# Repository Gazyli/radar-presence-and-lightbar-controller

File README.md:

# Custom ESPhome Devices for Home Assistant

This repository contains the hardware designs and custom firmware for two integrated smart home devices designed from scratch: a **mmWave radar presence sensor** and a **dual-channel CCT light controller**.

## Overview

The two devices are built around the ESP32-C3 microcontroller and are designed to seamlessly integrate with Home Assistant via ESPHome. The presence sensor utilizes advanced mmWave radar technology for accurate spatial tracking, while the light controller offers precise control over brightness and color temperature for LED lighting setups. Both devices are designed with modular firmware configurations to allow for easy customization and deployment across multiple nodes in a smart home environment.

## Devices

### 1. mmWave Radar Presence Sensor
A highly sensitive presence detection node utilizing mmWave radar technology (supporting LD2410C and LD2450 sensors).
* **Features**: Real-time spatial tracking with custom zone/target math logic, combined with integrated environmental monitoring (temperature, humidity, light levels).
* **Hardware**: Custom PCBs designed in KiCad, powered by ESP32-C3 microcontrollers.
* **Firmware**: Modular ESPHome configuration leveraging custom C++ headers (`radar_math.h`, `zone_math.h`) for complex tracking.

### 2. Dual-Channel CCT Light Controller (Lightbar)
A precision lighting controller tailored for dual-channel (warm/cool white) LED strips.
* **Features**: Precise, flicker-free adjustment of brightness and color temperature (CCT). Also supports ambient light sensors (e.g., BH1750) for dynamic lighting capabilities. Powered with USB-PD.
* **Hardware**: Custom KiCad schematic and PCB layout for LED driving and ESP32 control.
* **Firmware**: ESPHome configurations optimized for smooth dimming logic and color temperature transitions.

## Project Structure

* **`ESPhome/`**: Contains all firmware configurations and code.
  * `common/`: Reusable YAML fragments (base ESP32 setups, sensor integrations) and custom C++ header files used across multiple identical device nodes.
  * `lightbar/`: Deployment-specific configurations for the CCT light controllers.
  * `presence/`: Deployment-specific configurations for the presence sensors.
* **`schematics/`**: KiCad project files (`.kicad_sch`, `.kicad_pcb`) containing the circuit designs for both the presence sensor and light controller variants.
* **`enclosures/`**: 3D printable enclosure designs for both devices, including STL and 3MF files.

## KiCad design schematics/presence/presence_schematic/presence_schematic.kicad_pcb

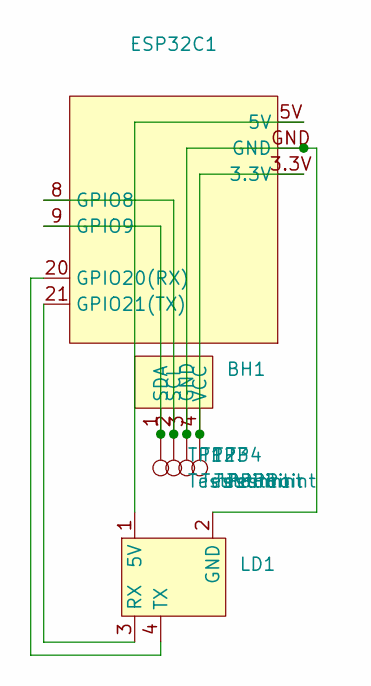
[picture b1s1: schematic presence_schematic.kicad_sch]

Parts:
BH1: BH1750
ESP32C1: ESP32-C3 supermini
LD1: LD2450
TP1, TP2, TP3, TP4: TestPoint; SolderWirePad_1x01_SMD_1.5x3mm

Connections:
unnamed: BH1.3 (GND), ESP32C1.GND, LD1.2 (GND), TP3.1
unnamed: BH1.2 (SCL), ESP32C1.8 (GPIO8), TP2.1
unnamed: BH1.1 (SDA), ESP32C1.9 (GPIO9), TP1.1
unnamed: BH1.4 (VCC), ESP32C1.3.3V, TP4.1
unnamed: ESP32C1.20 (GPIO20(RX)), LD1.4 (TX)
unnamed: ESP32C1.21 (GPIO21(TX)), LD1.3 (RX)
unnamed: ESP32C1.5V, LD1.1 (5V)

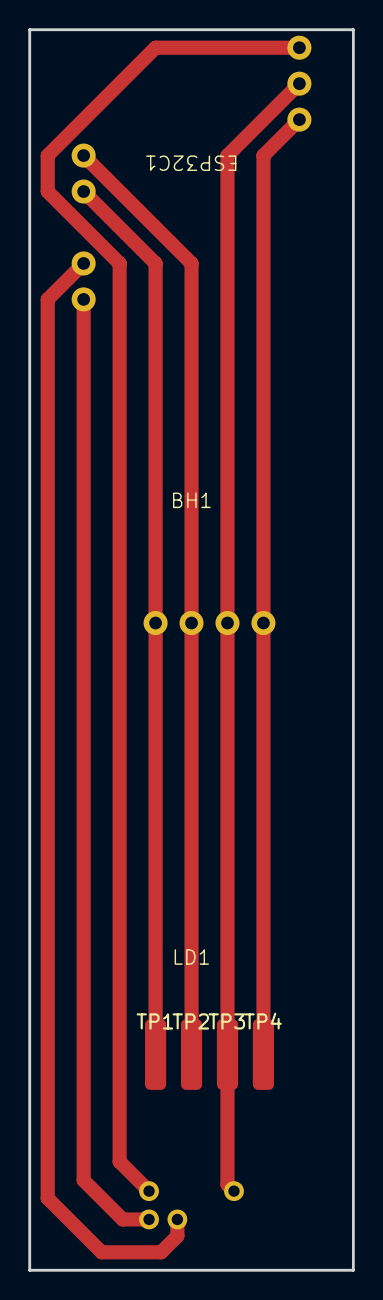
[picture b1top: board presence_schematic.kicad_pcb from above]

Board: 2 copper layers, 22.9 x 87.6 mm, 7 parts (0 on the bottom side), 7 nets.

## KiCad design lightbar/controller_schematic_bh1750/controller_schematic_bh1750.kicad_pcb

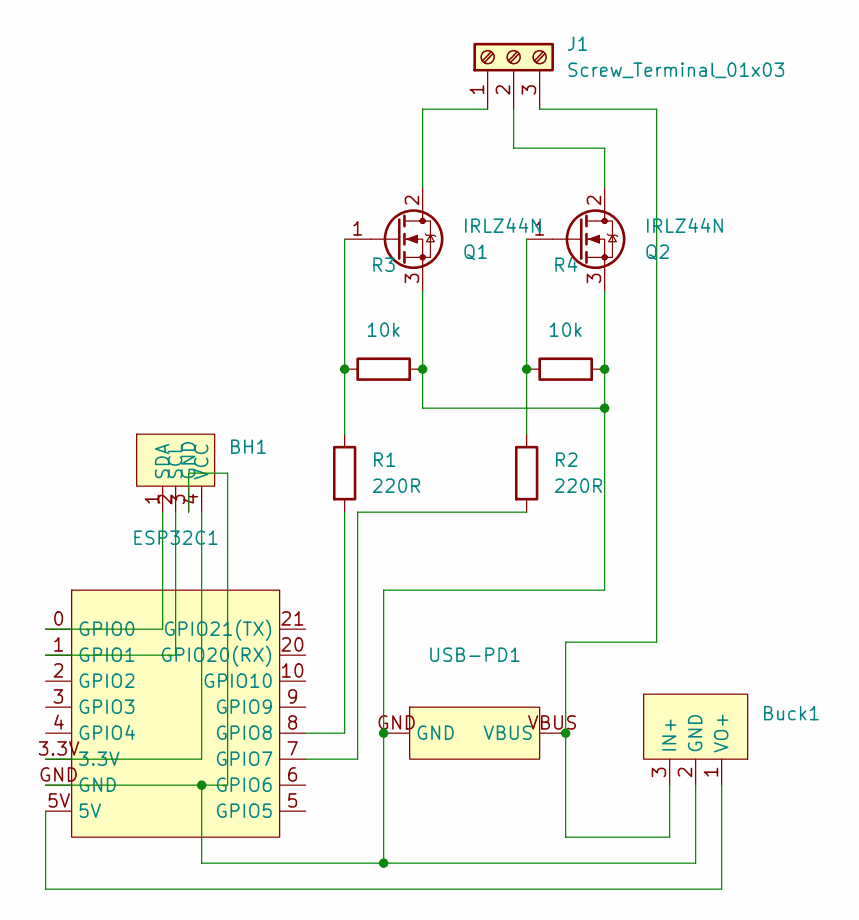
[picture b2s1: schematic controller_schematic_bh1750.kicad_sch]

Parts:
BH1: BH1750
Buck1: Buck_converter
ESP32C1: ESP32-C3 supermini
J1: Screw_Terminal_01x03; 3 pin screw connector
Q1, Q2: IRLZ44N; TO-220-3_Horizontal_TabDown
R1, R2: 220R; R_Axial_DIN0207_L6.3mm_D2.5mm_P7.62mm_Horizontal
R3, R4: 10k; R_Axial_DIN0207_L6.3mm_D2.5mm_P7.62mm_Horizontal
USB-PD1: USB-PD board

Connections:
unnamed: BH1.3 (GND), Buck1.2 (GND), ESP32C1.GND, Q1.3 (S), Q2.3 (S), R3.2, R4.2, USB-PD1.GND
unnamed: BH1.2 (SCL), ESP32C1.1 (GPIO1)
unnamed: BH1.1 (SDA), ESP32C1.0 (GPIO0)
unnamed: BH1.4 (VCC), ESP32C1.3.3V
unnamed: Buck1.3 (IN+), J1.3, USB-PD1.VBUS
unnamed: Buck1.1 (VO+), ESP32C1.5V
unnamed: ESP32C1.7 (GPIO7), R2.2
unnamed: ESP32C1.8 (GPIO8), R1.2
unnamed: J1.1, Q1.2 (D)
unnamed: J1.2, Q2.2 (D)
unnamed: Q1.1 (G), R1.1, R3.1
unnamed: Q2.1 (G), R2.1, R4.1

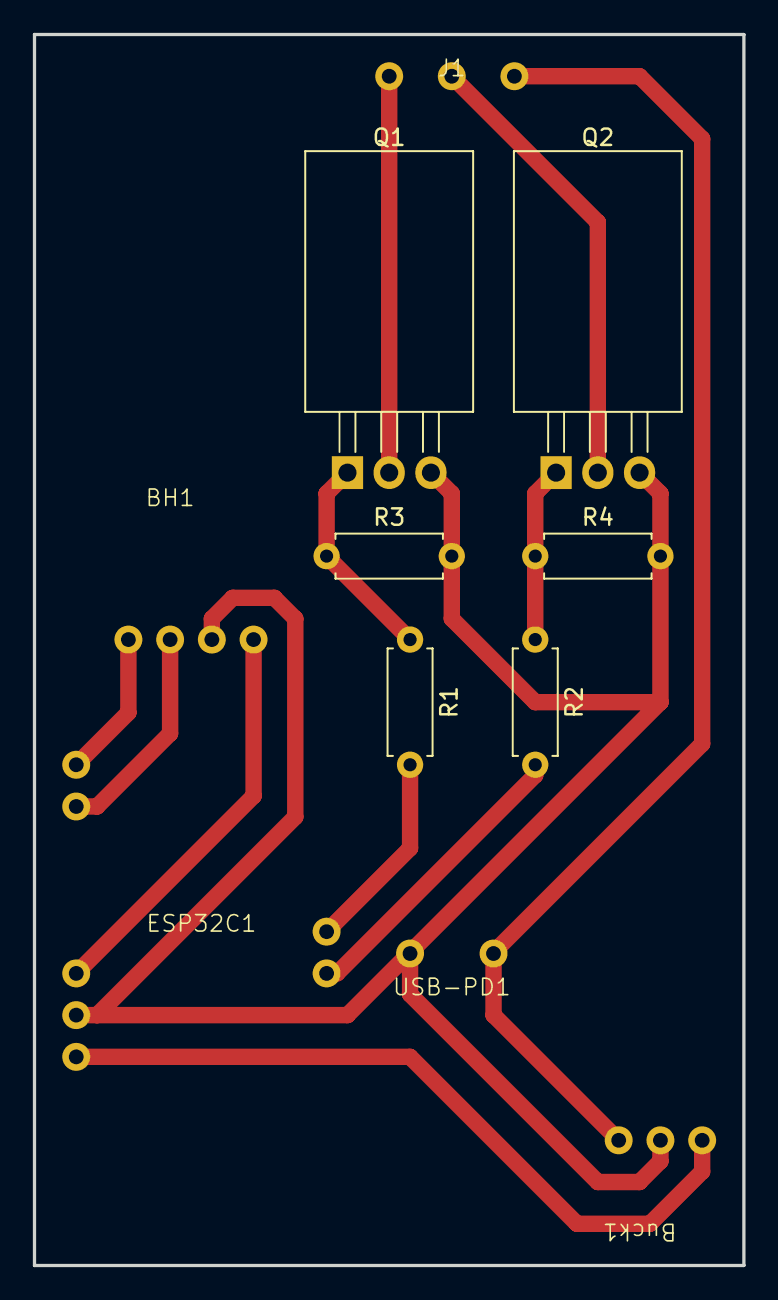
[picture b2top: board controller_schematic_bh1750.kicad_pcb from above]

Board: 2 copper layers, 43.2 x 74.9 mm, 11 parts (0 on the bottom side), 12 nets.

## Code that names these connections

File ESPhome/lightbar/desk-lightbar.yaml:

esphome:
  name: desk-lightbar
  friendly_name: "Desk Lightbar"
  area: "Desk"

substitutions:
  # Lightbar
  cold_white_pin: "GPIO7"
  warm_white_pin: "GPIO8"
  # Atmospheric
  i2c_sda_pin: "GPIO0"
  i2c_scl_pin: "GPIO1"

packages:
  common_esp32c3_setup: !include ../common/esp32c3-base.yaml
  common_diagnostics: !include ../common/diagnostics.yaml
  common_lightbar: !include ../common/lightbar.yaml
  common_illuminance: !include ../common/bh1750.yaml

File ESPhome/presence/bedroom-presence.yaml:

esphome:
  name: bedroom-presence
  friendly_name: "Bedroom Presence"
  area: "Bedroom"

substitutions:
  # Presence
  uart_tx_pin: "GPIO21"
  uart_rx_pin: "GPIO20"
  # Atmospheric
  i2c_sda_pin: "GPIO9"
  i2c_scl_pin: "GPIO8"

packages:
  common_esp32c3_setup: !include ../common/esp32c3-base.yaml
  common_diagnostics: !include ../common/diagnostics.yaml
  common_presence: !include ../common/presence-LD2450.yaml
  common_atmospheric: !include ../common/atmospheric.yaml

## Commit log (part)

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2026-03-03 initial HA configs commit
2026-03-05 working no-zone presence config
2026-03-13 new schematics and lightbar pins
2026-03-14 global coordinate radar
2026-03-14 common LD2450 presence config
2026-03-14 modular common packages for setup, diagnostics and two radar variants
2026-03-14 common lighbar packages
2026-03-14 minor updates
2026-03-15 schematic updates
2026-03-19 Generalized common packages with substitutions
2026-03-19 schematic directory refactor
2026-03-19 Zone setup template package
2026-03-19 Moved target global coordinates to a template
2026-03-19 updated coordinate calculation speed and smoothing, small zone logic changes
2026-04-06 Initial README version
2026-04-25 Add image of sensor PCBs to README
2026-05-09 Lightbar controller enclosure 3d files
